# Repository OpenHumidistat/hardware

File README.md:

# OpenHumidistat hardware
This repository contains the KiCAD design files for two PCBs for the OpenHumidistat humidity controller.

## References
### KiCAD symbols, footprints, and models:
- Teensy LC microcontroller board:
  - [Symbol](https://github.com/XenGi/teensy_library)
  - [Footprint](https://github.com/XenGi/teensy.pretty)
  - [3D model](https://grabcad.com/library/teensy-lc-1)
- TO-220 aluminium heatsink:
  - [3D model](https://grabcad.com/library/heat-sink-to-220-1)

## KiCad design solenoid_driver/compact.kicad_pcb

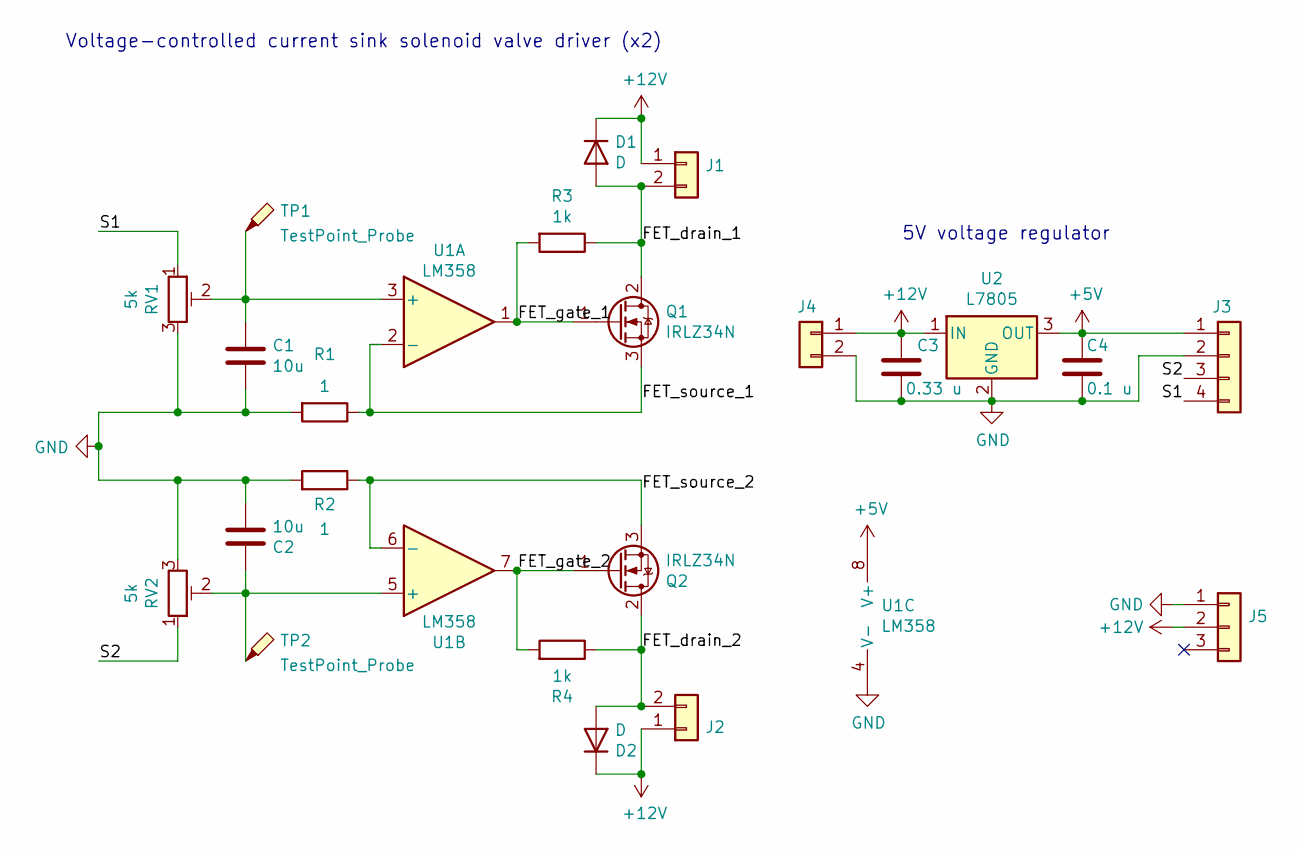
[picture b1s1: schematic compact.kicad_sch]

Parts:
C1, C2: 10u; C_Disc_D7.5mm_W5.0mm_P5.00mm
C3: 0.33 u; C_Disc_D4.3mm_W1.9mm_P5.00mm
C4: 0.1 u; C_Disc_D4.3mm_W1.9mm_P5.00mm
D1, D2: D; D_DO-41_SOD81_P10.16mm_Horizontal
J1, J2, J4: Conn_01x02; JST_XH_B2B-XH-A_1x02_P2.50mm_Vertical
J3: Conn_01x04; PinHeader_1x04_P2.54mm_Vertical
J5: Conn_01x03; Molex_KK-254_AE-6410-03A_1x03_P2.54mm_Vertical
Q1, Q2: IRLZ34N; TO-220-3_Vertical_heatsink
R1, R2: 1; R_Axial_DIN0516_L15.5mm_D5.0mm_P20.32mm_Horizontal
R3, R4: 1k; R_Axial_DIN0207_L6.3mm_D2.5mm_P10.16mm_Horizontal
RV1, RV2: 5k; Potentiometer_Bourns_3296W_Vertical
TP1, TP2: TestPoint_Probe; TestPoint_THTPad_D1.0mm_Drill0.5mm
U1: LM358; DIP-8_W7.62mm
U2: L7805; TO-220-3_Vertical_heatsink

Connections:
+5V: C4.1, J3.1, U1.8 (V+), U2.3 (OUT)
+12V: C3.1, D1.1 (K), D2.1 (K), J1.1, J2.1, J4.1, J5.2, U2.1 (IN)
/FET_drain_1: D1.2 (A), J1.2, Q1.2 (D), R3.1
/FET_drain_2: D2.2 (A), J2.2, Q2.2 (D), R4.1
/FET_gate_1: Q1.1 (G), R3.2, U1.1
/FET_gate_2: Q2.1 (G), R4.2, U1.7
/FET_source_1: Q1.3 (S), R1.1, U1.2 (-)
/FET_source_2: Q2.3 (S), R2.1, U1.6 (-)
/S1: J3.4, RV1.1
/S2: J3.3, RV2.1
GND: C1.2, C2.2, C3.2, C4.2, J3.2, J4.2, J5.1, R1.2, R2.2, RV1.3, RV2.3, U1.4 (V-), U2.2 (GND)
unnamed: C1.1, RV1.2, TP1.1, U1.3 (+)
unnamed: C2.1, RV2.2, TP2.1, U1.5 (+)

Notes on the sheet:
Voltage-controlled current sink solenoid valve driver (x2)
5V voltage regulator

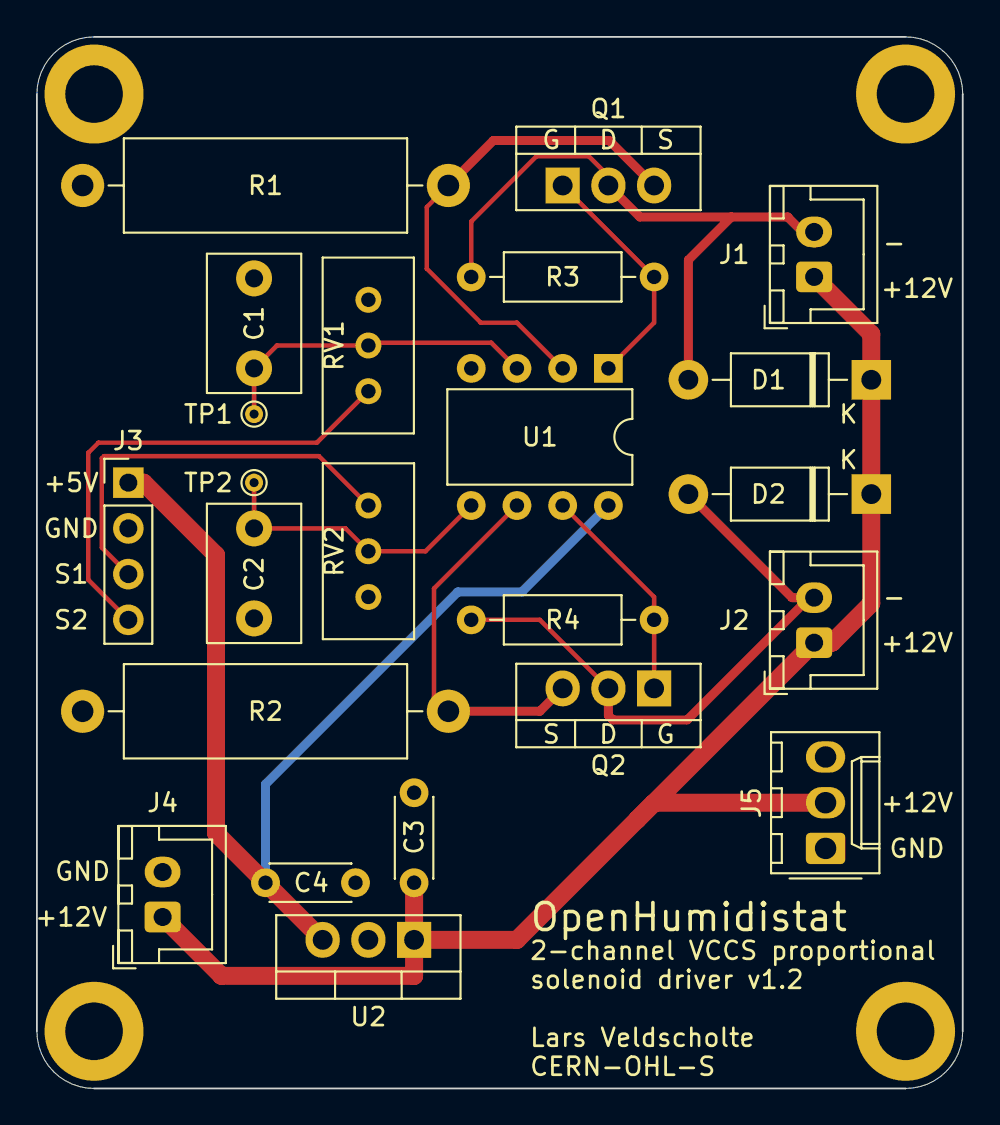
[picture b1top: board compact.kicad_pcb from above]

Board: 2 copper layers, 51.4 x 58.4 mm, 23 parts (0 on the bottom side), 13 nets.

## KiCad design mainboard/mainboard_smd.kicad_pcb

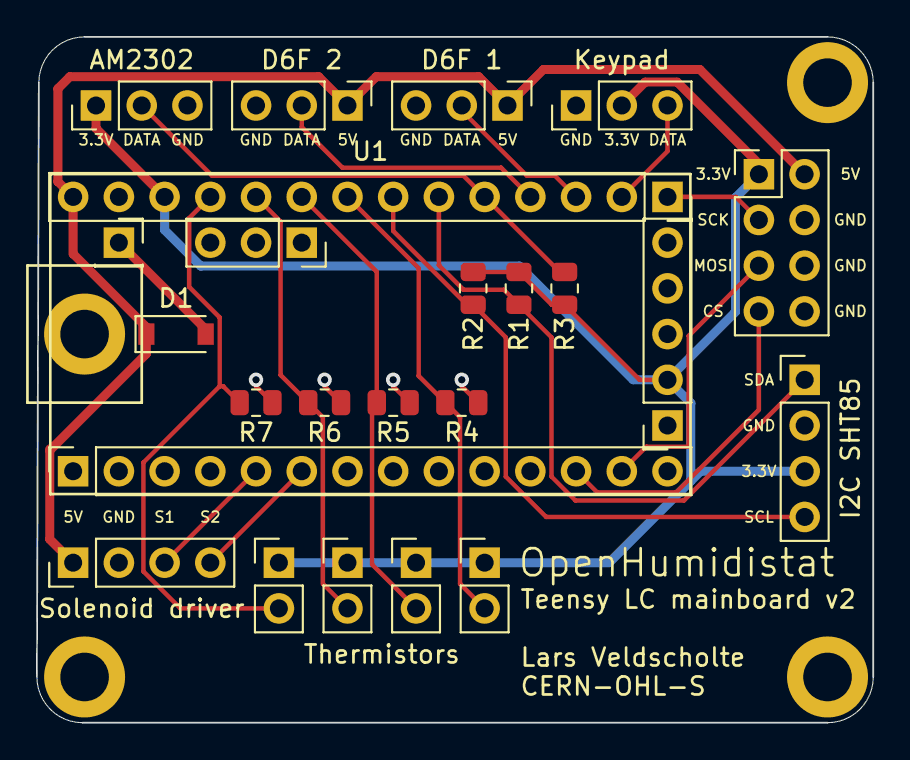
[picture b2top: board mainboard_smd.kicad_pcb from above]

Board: 2 copper layers, 46.5 x 38.1 mm, 25 parts (0 on the bottom side), 19 nets.

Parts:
D1: 1N5817; D_SOD-123
J1, J2: Conn_01x14; PinSocket_1x14_P2.54mm_Vertical
J3: Conn_01x05; PinSocket_1x05_P2.54mm_Vertical
J4: Conn_01x03; PinSocket_1x03_P2.54mm_Vertical
J5: Conn_01x01; PinSocket_1x01_P2.54mm_Vertical
J6: Keypad; PinHeader_1x03_P2.54mm_Vertical
J7: D6F 2; PinHeader_1x03_P2.54mm_Vertical
J8: D6F 1; PinHeader_1x03_P2.54mm_Vertical
J9: SPI LCD; PinHeader_2x04_P2.54mm_Vertical
J10: I2C SHT85; PinHeader_1x04_P2.54mm_Vertical
J11: Solenoid driver; PinHeader_1x04_P2.54mm_Vertical
J12: AM2302; PinHeader_1x03_P2.54mm_Vertical
J13, J14, J15, J16: Conn_01x02; PinHeader_1x02_P2.54mm_Vertical
R1, R2, R3: 4.7k; R_0805_2012Metric
R4, R5, R6, R7: 10k; R_0805_2012Metric
U1: Teensy-LC; Teensy_LC

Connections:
+3V3: J2.12, J3.2, J6.2, J9.1, J10.3, J12.1, J13.1, J14.1, J15.1, J16.1, R1.1, R2.1, R3.2
+5V: D1.1 (K), J2.14, J7.1, J8.1, J9.2, J11.1
/3: J1.5, J11.3
/4: J1.6, J11.4
/10_CS0: J1.12, J9.7
/11_MOSI0: J1.13, J9.5
/13_LED_SCK0: J2.1, J9.3
/14_A0: J2.2, J6.3
/15_A1: J2.3, J8.2
/16_A2: J2.4, J7.2
/17_A3: J2.5, J12.2, R3.1
/18_A4_SDA0: J2.6, J10.1, R1.2
/19_A5_SCL0: J2.7, J10.4, R2.2
/20_A6_SCK1: J2.8, J13.2, R4.2
/21_A7: J2.9, J14.2, R5.2
/22_A8_SCL1: J2.10, J15.2, R6.2
/23_A9_SDA1: J2.11, J16.2, R7.2
GND: J1.1, J2.13, J3.3, J6.1, J7.3, J8.3, J9.4, J9.6, J9.8, J10.2, J11.2, J12.3, R4.1, R5.1, R6.1, R7.1
VBUS: D1.2 (A), J5.1

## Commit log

2021-12-06 Add KiCAD projects
2023-10-10 Add fan header to solenoid driver PCB

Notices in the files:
mainboard/mainboard_smd.kicad_pcb:
CERN-OHL-S
